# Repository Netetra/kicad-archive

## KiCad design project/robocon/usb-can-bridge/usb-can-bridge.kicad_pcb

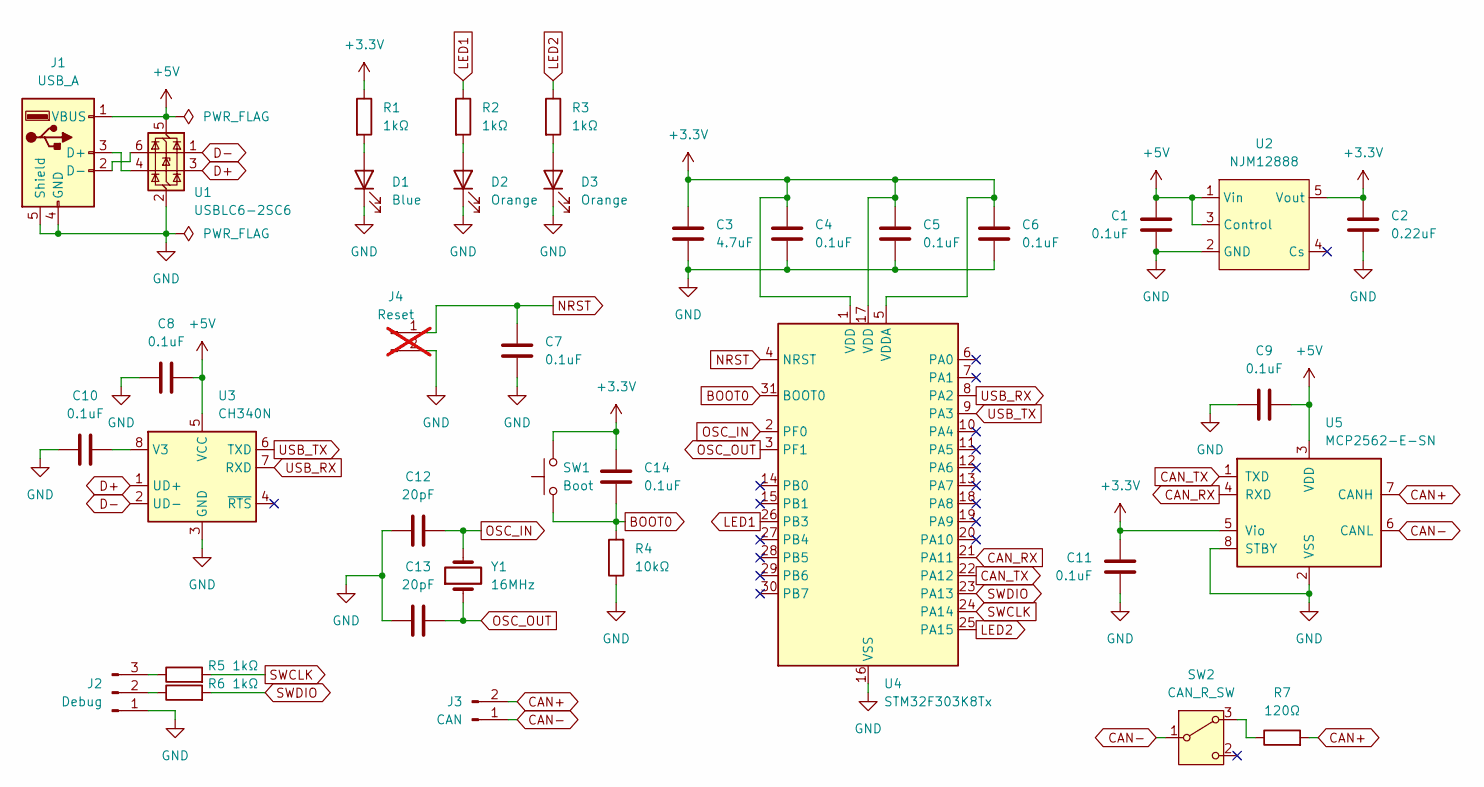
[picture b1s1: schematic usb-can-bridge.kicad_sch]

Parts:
C1, C4, C5, C6, C7, C8, C9, C10, C11, C14: 0.1uF; C_0603_1608Metric
C2: 0.22uF; C_0603_1608Metric
C3: 4.7uF; C_0603_1608Metric
C12, C13: 20pF; C_0603_1608Metric
D1: Blue; LED_0603_1608Metric
D2, D3: Orange; LED_0603_1608Metric
J1: USB_A; USB_A_CNCTech_1001-011-01101_Horizontal
J2: Debug; PinSocket_1x03_P2.54mm_Horizontal
J3: CAN; JST_XH_S2B-XH-A_1x02_P2.50mm_Horizontal
J4: Reset; PinSocket_1x02_P1.27mm_Vertical; not fitted
R1, R2, R3, R5, R6: 1kΩ; R_0603_1608Metric
R4: 10kΩ; R_0603_1608Metric
R7: 120Ω; R_0603_1608Metric
SW1: Boot; SW_PUSH_1P1T_6x3.5mm_H4.3_APEM_MJTP1243
SW2: CAN_R_SW; SW_Slide-03_Wuerth-WS-SLTV_10x2.5x6.4_P2.54mm
U1: USBLC6-2SC6; SOT-23-6
U2: NJM12888; SOT-23-5
U3: CH340N; JEITA_SOIC-8_3.9x4.9mm_P1.27mm
U4: STM32F303K8Tx; LQFP-32_7x7mm_P0.8mm
U5: MCP2562-E-SN; SOIC-8_3.9x4.9mm_P1.27mm
Y1: 16MHz; Crystal_HC49-4H_Vertical

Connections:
+3.3V: C2.1, C3.1, C4.1, C5.1, C6.1, C11.1, C14.1, R1.1, SW1.2, U2.5 (Vout), U4.1 (VDD), U4.5 (VDDA), U4.17 (VDD), U5.5 (Vio)
+5V: C1.1, C8.2, C9.2, J1.1 (VBUS), U1.5 (VBUS), U2.1 (Vin), U2.3 (Control), U3.5 (VCC), U5.3 (VDD)
BOOT0: C14.2, R4.2, SW1.1, U4.31 (BOOT0)
CAN+: J3.2, R7.2, U5.7 (CANH)
CAN-: J3.1, SW2.1 (B), U5.6 (CANL)
CAN_RX: U4.21 (PA11), U5.4 (RXD)
CAN_TX: U4.22 (PA12), U5.1 (TXD)
D+: U1.3 (I/O2), U3.1 (UD+)
D-: U1.1 (I/O1), U3.2 (UD-)
GND: C1.2, C2.2, C3.2, C4.2, C5.2, C6.2, C7.2, C8.1, C9.1, C10.1, C11.2, C12.1, C13.1, D1.1 (K), D2.1 (K), D3.1 (K), J1.4 (GND), J1.5 (Shield), J2.1, J4.2, R4.1, U1.2 (GND), U2.2 (GND), U3.3 (GND), U4.16 (VSS), U4.32 (VSS), U5.2 (VSS), U5.8 (STBY)
LED1: R2.1, U4.26 (PB3)
LED2: R3.1, U4.25 (PA15)
NRST: C7.1, J4.1, U4.4 (NRST)
unnamed: D1.2 (A), R1.2
unnamed: D2.2 (A), R2.2
unnamed: D3.2 (A), R3.2
unnamed: J1.3 (D+), U1.4 (I/O2)
unnamed: J1.2 (D-), U1.6 (I/O1)
unnamed: J2.2, R6.1
unnamed: J2.3, R5.1
unnamed: R7.1, SW2.3 (A)
unnamed: C10.2, U3.8 (V3)
OSC_IN: C12.2, U4.2 (PF0), Y1.2
OSC_OUT: C13.2, U4.3 (PF1), Y1.1
SWCLK: R5.2, U4.24 (PA14)
SWDIO: R6.2, U4.23 (PA13)
USB_RX: U3.7 (RXD), U4.8 (PA2)
USB_TX: U3.6 (TXD), U4.9 (PA3)

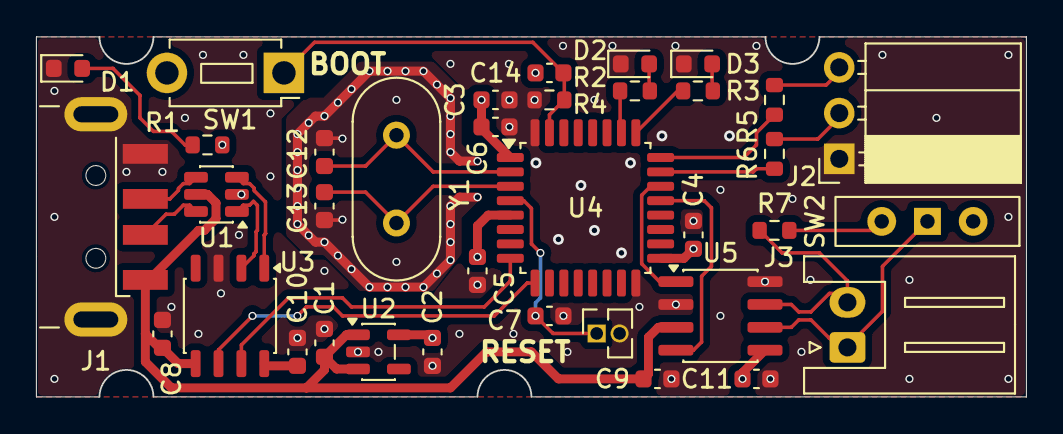
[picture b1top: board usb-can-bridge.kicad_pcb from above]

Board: 4 copper layers, 55.0 x 20.0 mm, 36 parts (0 on the bottom side), 28 nets.

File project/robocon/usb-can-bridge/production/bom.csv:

Designator,Footprint,Quantity,Value,LCSC Part #
"C1, C10, C11, C14, C4, C5, C6, C7, C8, C9",0603,10,0.1uF,
"C12, C13",0603,2,20pF,
C2,0603,1,0.22uF,
C3,0603,1,4.7uF,
D1,0603,1,Blue,
"D2, D3",0603,2,Orange,
J1,USB_A_CNCTech_1001-011-01101_Horizontal,1,USB_A,
J2,PinSocket_1x03_P2.54mm_Horizontal,1,Debug,
J3,JST_XH_S2B-XH-A_1x02_P2.50mm_Horizontal,1,CAN,
J4,PinSocket_1x02_P1.27mm_Vertical,1,Reset,
"R1, R2, R3, R5, R6",0603,5,1kΩ,
R4,0603,1,10kΩ,
R7,0603,1,120Ω,
SW1,SW_PUSH_1P1T_6x3.5mm_H4.3_APEM_MJTP1243,1,Boot,
SW2,SW_Slide-03_Wuerth-WS-SLTV_10x2.5x6.4_P2.54mm,1,CAN_R_SW,
U1,SOT-23-6,1,USBLC6-2SC6,
U2,SOT-23-5,1,NJM12888,
U3,JEITA_SOIC-8_3.9x4.9mm_P1.27mm,1,CH340N,
U4,LQFP-32_7x7mm_P0.8mm,1,STM32F303K8Tx,
U5,SOIC-8_3.9x4.9mm_P1.27mm,1,MCP2562-E-SN,
Y1,Crystal_HC49-4H_Vertical,1,16MHz,

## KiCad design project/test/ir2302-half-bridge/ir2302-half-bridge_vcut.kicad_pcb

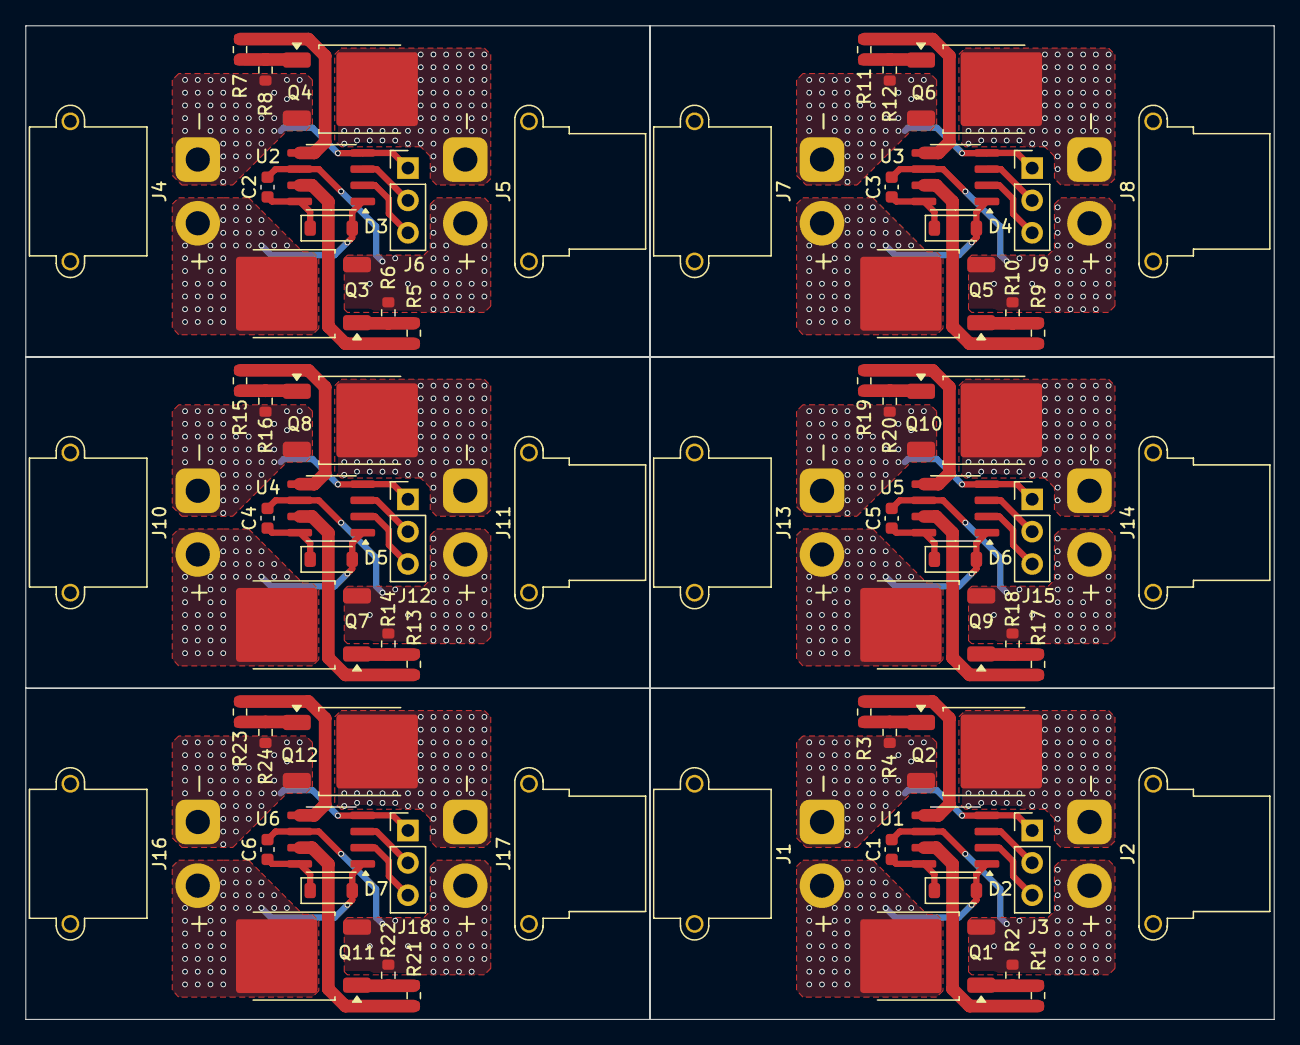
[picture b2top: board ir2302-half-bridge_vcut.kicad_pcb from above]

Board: 2 copper layers, 98.0 x 78.0 mm, 72 parts (0 on the bottom side), 11 nets.

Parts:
C1, C2, C3, C4, C5, C6: 0.1uF; C_0603_1608Metric
D2, D3, D4, D5, D6, D7: 1N4148W; D_SOD-123
J1, J4, J7, J10, J13, J16: Power; AMASS_XT30PW-M_1x02_P2.50mm_Horizontal
J2, J5, J8, J11, J14, J17: Output; AMASS_XT30PW-F_1x02_P2.50mm_Horizontal
J3, J6, J9, J12, J15, J18: Input; PinHeader_1x03_P2.54mm_Vertical
Q1, Q2, Q3, Q4, Q5, Q6, Q7, Q8, Q9, Q10, Q11, Q12: TK25S06N1L; TO-252-2
R1, R3, R5, R7, R9, R11, R13, R15, R17, R19, R21, R23: 10Ω; R_0603_1608Metric
R2, R4, R6, R8, R10, R12, R14, R16, R18, R20, R22, R24: 10kΩ; R_0603_1608Metric
U1, U2, U3, U4, U5, U6: IR2302; SOIC-8_3.9x4.9mm_P1.27mm

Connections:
+12V: D2.2 (A), D3.2 (A), D4.2 (A), D5.2 (A), D6.2 (A), D7.2 (A), J1.2, J4.2, J7.2, J10.2, J13.2, J16.2, Q1.2 (D), Q3.2 (D), Q5.2 (D), Q7.2 (D), Q9.2 (D), Q11.2 (D), U1.1 (VCC), U2.1 (VCC), U3.1 (VCC), U4.1 (VCC), U5.1 (VCC), U6.1 (VCC)
GND: J1.1, J3.1, J4.1, J6.1, J7.1, J9.1, J10.1, J12.1, J13.1, J15.1, J16.1, J18.1, Q2.3 (S), Q4.3 (S), Q6.3 (S), Q8.3 (S), Q10.3 (S), Q12.3 (S), R4.2, R8.2, R12.2, R16.2, R20.2, R24.2, U1.4 (COM), U2.4 (COM), U3.4 (COM), U4.4 (COM), U5.4 (COM), U6.4 (COM)
unnamed: C1.1, C2.1, C3.1, C4.1, C5.1, C6.1, D2.1 (K), D3.1 (K), D4.1 (K), D5.1 (K), D6.1 (K), D7.1 (K), U1.8 (VB), U2.8 (VB), U3.8 (VB), U4.8 (VB), U5.8 (VB), U6.8 (VB)
unnamed: J2.1, J5.1, J8.1, J11.1, J14.1, J17.1, Q2.2 (D), Q4.2 (D), Q6.2 (D), Q8.2 (D), Q10.2 (D), Q12.2 (D)
unnamed: C1.2, C2.2, C3.2, C4.2, C5.2, C6.2, J2.2, J5.2, J8.2, J11.2, J14.2, J17.2, Q1.3 (S), Q3.3 (S), Q5.3 (S), Q7.3 (S), Q9.3 (S), Q11.3 (S), R2.2, R6.2, R10.2, R14.2, R18.2, R22.2, U1.6 (VS), U2.6 (VS), U3.6 (VS), U4.6 (VS), U5.6 (VS), U6.6 (VS)
unnamed: J3.2, J6.2, J9.2, J12.2, J15.2, J18.2, U1.3 (~SD), U2.3 (~SD), U3.3 (~SD), U4.3 (~SD), U5.3 (~SD), U6.3 (~SD)
unnamed: J3.3, J6.3, J9.3, J12.3, J15.3, J18.3, U1.2 (IN), U2.2 (IN), U3.2 (IN), U4.2 (IN), U5.2 (IN), U6.2 (IN)
unnamed: Q1.1 (G), Q3.1 (G), Q5.1 (G), Q7.1 (G), Q9.1 (G), Q11.1 (G), R1.2, R2.1, R5.2, R6.1, R9.2, R10.1, R13.2, R14.1, R17.2, R18.1, R21.2, R22.1
unnamed: Q2.1 (G), Q4.1 (G), Q6.1 (G), Q8.1 (G), Q10.1 (G), Q12.1 (G), R3.2, R4.1, R7.2, R8.1, R11.2, R12.1, R15.2, R16.1, R19.2, R20.1, R23.2, R24.1
unnamed: R1.1, R5.1, R9.1, R13.1, R17.1, R21.1, U1.7 (HO), U2.7 (HO), U3.7 (HO), U4.7 (HO), U5.7 (HO), U6.7 (HO)
unnamed: R3.1, R7.1, R11.1, R15.1, R19.1, R23.1, U1.5 (LO), U2.5 (LO), U3.5 (LO), U4.5 (LO), U5.5 (LO), U6.5 (LO)

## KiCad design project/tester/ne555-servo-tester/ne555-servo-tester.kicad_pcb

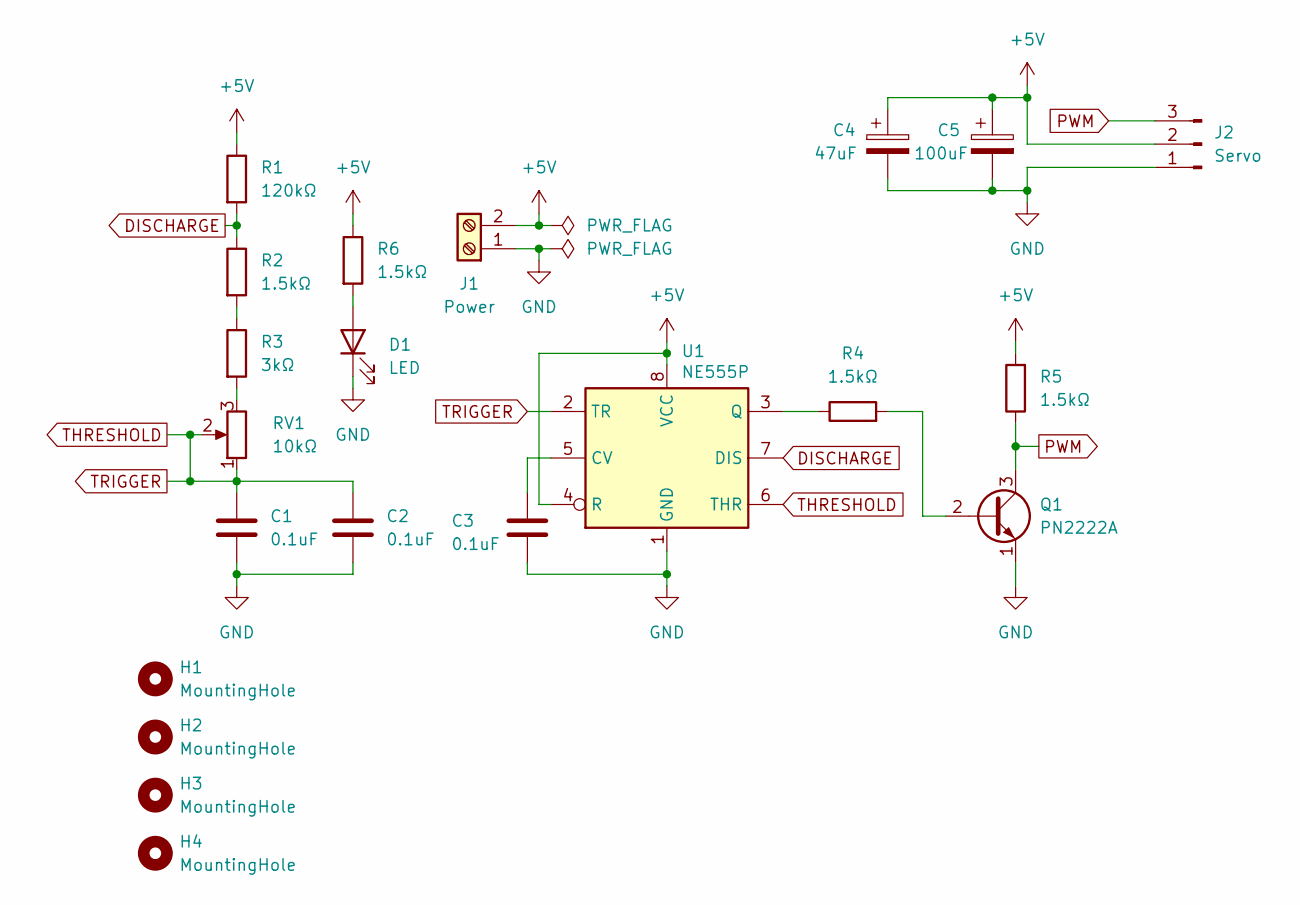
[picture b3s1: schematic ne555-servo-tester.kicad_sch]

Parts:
C1, C2, C3: 0.1uF; C_Disc_D3.0mm_W2.0mm_P2.50mm
C4: 47uF; CP_Radial_D6.3mm_P2.50mm
C5: 100uF; CP_Radial_D6.3mm_P2.50mm
D1: LED; LED_D5.0mm
H1, H2, H3, H4: MountingHole; MountingHole_3.2mm_M3
J1: Power; TerminalBlock_MetzConnect_Type101_RT01602HBWC_1x02_P5.08mm_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
J2: Servo; PinHeader_1x03_P2.54mm_Vertical
Q1: PN2222A; TO-92_Inline
R1: 120kΩ; R_Axial_DIN0207_L6.3mm_D2.5mm_P10.16mm_Horizontal
R2, R4, R5, R6: 1.5kΩ; R_Axial_DIN0207_L6.3mm_D2.5mm_P10.16mm_Horizontal
R3: 3kΩ; R_Axial_DIN0207_L6.3mm_D2.5mm_P10.16mm_Horizontal
RV1: 10kΩ; Potentiometer_Piher_PT-6-V_Vertical
U1: NE555P; DIP-8_W7.62mm

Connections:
+5V: C4.1, C5.1, J1.2, J2.2, R1.1, R5.2, R6.1, U1.4 (R), U1.8 (VCC)
DISCHARGE: R1.2, R2.1, U1.7 (DIS)
GND: C1.2, C2.2, C3.2, C4.2, C5.2, D1.1 (K), J1.1, J2.1, Q1.1 (E), U1.1 (GND)
unnamed: D1.2 (A), R6.2
unnamed: Q1.2 (B), R4.2
unnamed: R2.2, R3.1
unnamed: R3.2, RV1.3
unnamed: C3.1, U1.5 (CV)
unnamed: R4.1, U1.3 (Q)
PWM: J2.3, Q1.3 (C), R5.1
THRESHOLD: C1.1, C2.1, RV1.1, RV1.2, U1.2 (TR), U1.6 (THR)

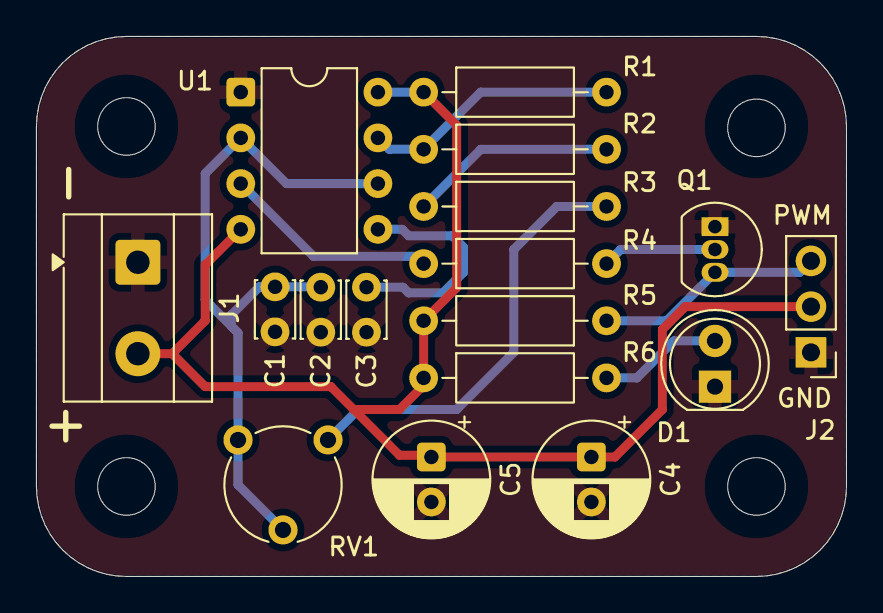
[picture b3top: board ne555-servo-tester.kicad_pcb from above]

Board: 2 copper layers, 45.0 x 30.0 mm, 21 parts (0 on the bottom side), 11 nets.

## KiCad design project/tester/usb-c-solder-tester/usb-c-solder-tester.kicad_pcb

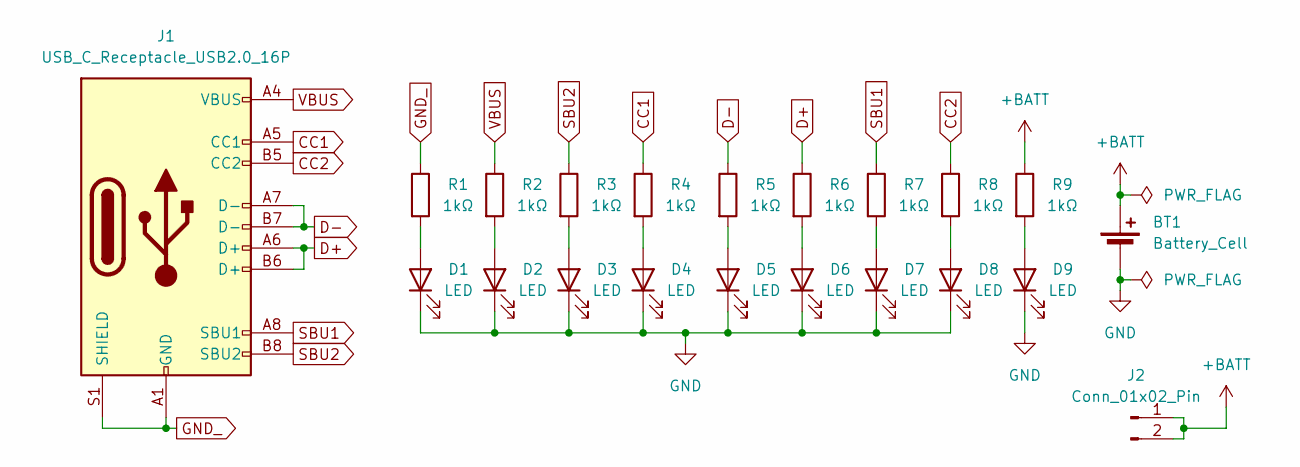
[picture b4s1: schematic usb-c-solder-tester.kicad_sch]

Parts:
BT1: Battery_Cell; CH25-2032LF
D1, D2, D3, D4, D5, D6, D7, D8, D9: LED; LED_0603_1608Metric
J1: USB_C_Receptacle_USB2.0_16P; USB_C_Receptacle_HRO_TYPE-C-31-M-12
J2: Conn_01x02_Pin; PinHeader_1x02_P2.54mm_Horizontal
R1, R2, R3, R4, R5, R6, R7, R8, R9: 1kΩ; R_0603_1608Metric

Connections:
+BATT: BT1.1 (+), J2.1, J2.2, R9.1
CC1: J1.A5 (CC1), R4.1
CC2: J1.B5 (CC2), R8.1
D+: J1.A6 (D+), J1.B6 (D+), R6.1
D-: J1.A7 (D-), J1.B7 (D-), R5.1
GND: BT1.2 (-), D1.1 (K), D2.1 (K), D3.1 (K), D4.1 (K), D5.1 (K), D6.1 (K), D7.1 (K), D8.1 (K), D9.1 (K)
GND_: J1.A1 (GND), J1.A12 (GND), J1.B1 (GND), J1.B12 (GND), J1.S1 (SHIELD), R1.1
unnamed: D1.2 (A), R1.2
unnamed: D2.2 (A), R2.2
unnamed: D3.2 (A), R3.2
unnamed: D4.2 (A), R4.2
unnamed: D5.2 (A), R5.2
unnamed: D6.2 (A), R6.2
unnamed: D7.2 (A), R7.2
unnamed: D8.2 (A), R8.2
unnamed: D9.2 (A), R9.2
SBU1: J1.A8 (SBU1), R7.1
SBU2: J1.B8 (SBU2), R3.1
VBUS: J1.A4 (VBUS), J1.A9 (VBUS), J1.B4 (VBUS), J1.B9 (VBUS), R2.1

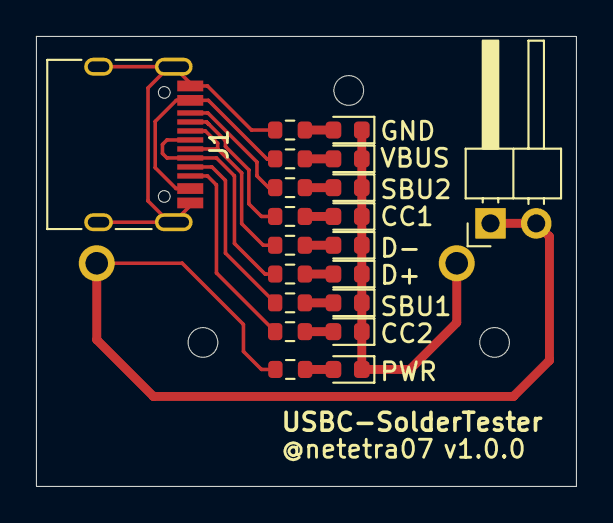
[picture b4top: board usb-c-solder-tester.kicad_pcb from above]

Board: 2 copper layers, 30.0 x 25.0 mm, 21 parts (1 on the bottom side), 19 nets.

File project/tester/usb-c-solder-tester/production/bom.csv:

Designator,Footprint,Quantity,Value,LCSC Part #
"BT1_12, BT1_11, BT1_10, BT1_9, BT1_8, BT1_7, BT1_6, BT1_5, BT1_4, BT1_3, BT1_2, BT1",CH25-2032LF,12,Battery_Cell,
"D1_12, D1_11, D1_10, D1_9, D1_8, D1_7, D1_6, D1_5, D1_4, D1_3, D1_2, D1, D2_12, D2_11, D2_10, D2_9, D2_8, D2_7, D2_6, D2_5, D2_4, D2_3, D2_2, D2, D3_12, D3_11, D3_10, D3_9, D3_8, D3_7, D3_6, D3_5, D3_4, D3_3, D3_2, D3, D4_12, D4_11, D4_10, D4_9, D4_8, D4_7, D4_6, D4_5, D4_4, D4_3, D4_2, D4, D5_12, D5_11, D5_10, D5_9, D5_8, D5_7, D5_6, D5_5, D5_4, D5_3, D5_2, D5, D6_12, D6_11, D6_10, D6_9, D6_8, D6_7, D6_6, D6_5, D6_4, D6_3, D6_2, D6, D7_12, D7_11, D7_10, D7_9, D7_8, D7_7, D7_6, D7_5, D7_4, D7_3, D7_2, D7, D8_12, D8_11, D8_10, D8_9, D8_8, D8_7, D8_6, D8_5, D8_4, D8_3, D8_2, D8, D9_12, D9_11, D9_10, D9_9, D9_8, D9_7, D9_6, D9_5, D9_4, D9_3, D9_2, D9",0603,108,LED,
"J1_12, J1_11, J1_10, J1_9, J1_8, J1_7, J1_6, J1_5, J1_4, J1_3, J1_2, J1",USB_C_Receptacle_HRO_TYPE-C-31-M-12,12,USB_C_Receptacle_USB2.0_16P,
"J2_12, J2_11, J2_10, J2_9, J2_8, J2_7, J2_6, J2_5, J2_4, J2_3, J2_2, J2",PinHeader_1x02_P2.54mm_Horizontal,12,Conn_01x02_Pin,
"R1_12, R1_11, R1_10, R1_9, R1_8, R1_7, R1_6, R1_5, R1_4, R1_3, R1_2, R1, R2_12, R2_11, R2_10, R2_9, R2_8, R2_7, R2_6, R2_5, R2_4, R2_3, R2_2, R2, R3_12, R3_11, R3_10, R3_9, R3_8, R3_7, R3_6, R3_5, R3_4, R3_3, R3_2, R3, R4_12, R4_11, R4_10, R4_9, R4_8, R4_7, R4_6, R4_5, R4_4, R4_3, R4_2, R4, R5_12, R5_11, R5_10, R5_9, R5_8, R5_7, R5_6, R5_5, R5_4, R5_3, R5_2, R5, R6_12, R6_11, R6_10, R6_9, R6_8, R6_7, R6_6, R6_5, R6_4, R6_3, R6_2, R6, R7_12, R7_11, R7_10, R7_9, R7_8, R7_7, R7_6, R7_5, R7_4, R7_3, R7_2, R7, R8_12, R8_11, R8_10, R8_9, R8_8, R8_7, R8_6, R8_5, R8_4, R8_3, R8_2, R8, R9_12, R9_11, R9_10, R9_9, R9_8, R9_7, R9_6, R9_5, R9_4, R9_3, R9_2, R9",0603,108,1kΩ,
